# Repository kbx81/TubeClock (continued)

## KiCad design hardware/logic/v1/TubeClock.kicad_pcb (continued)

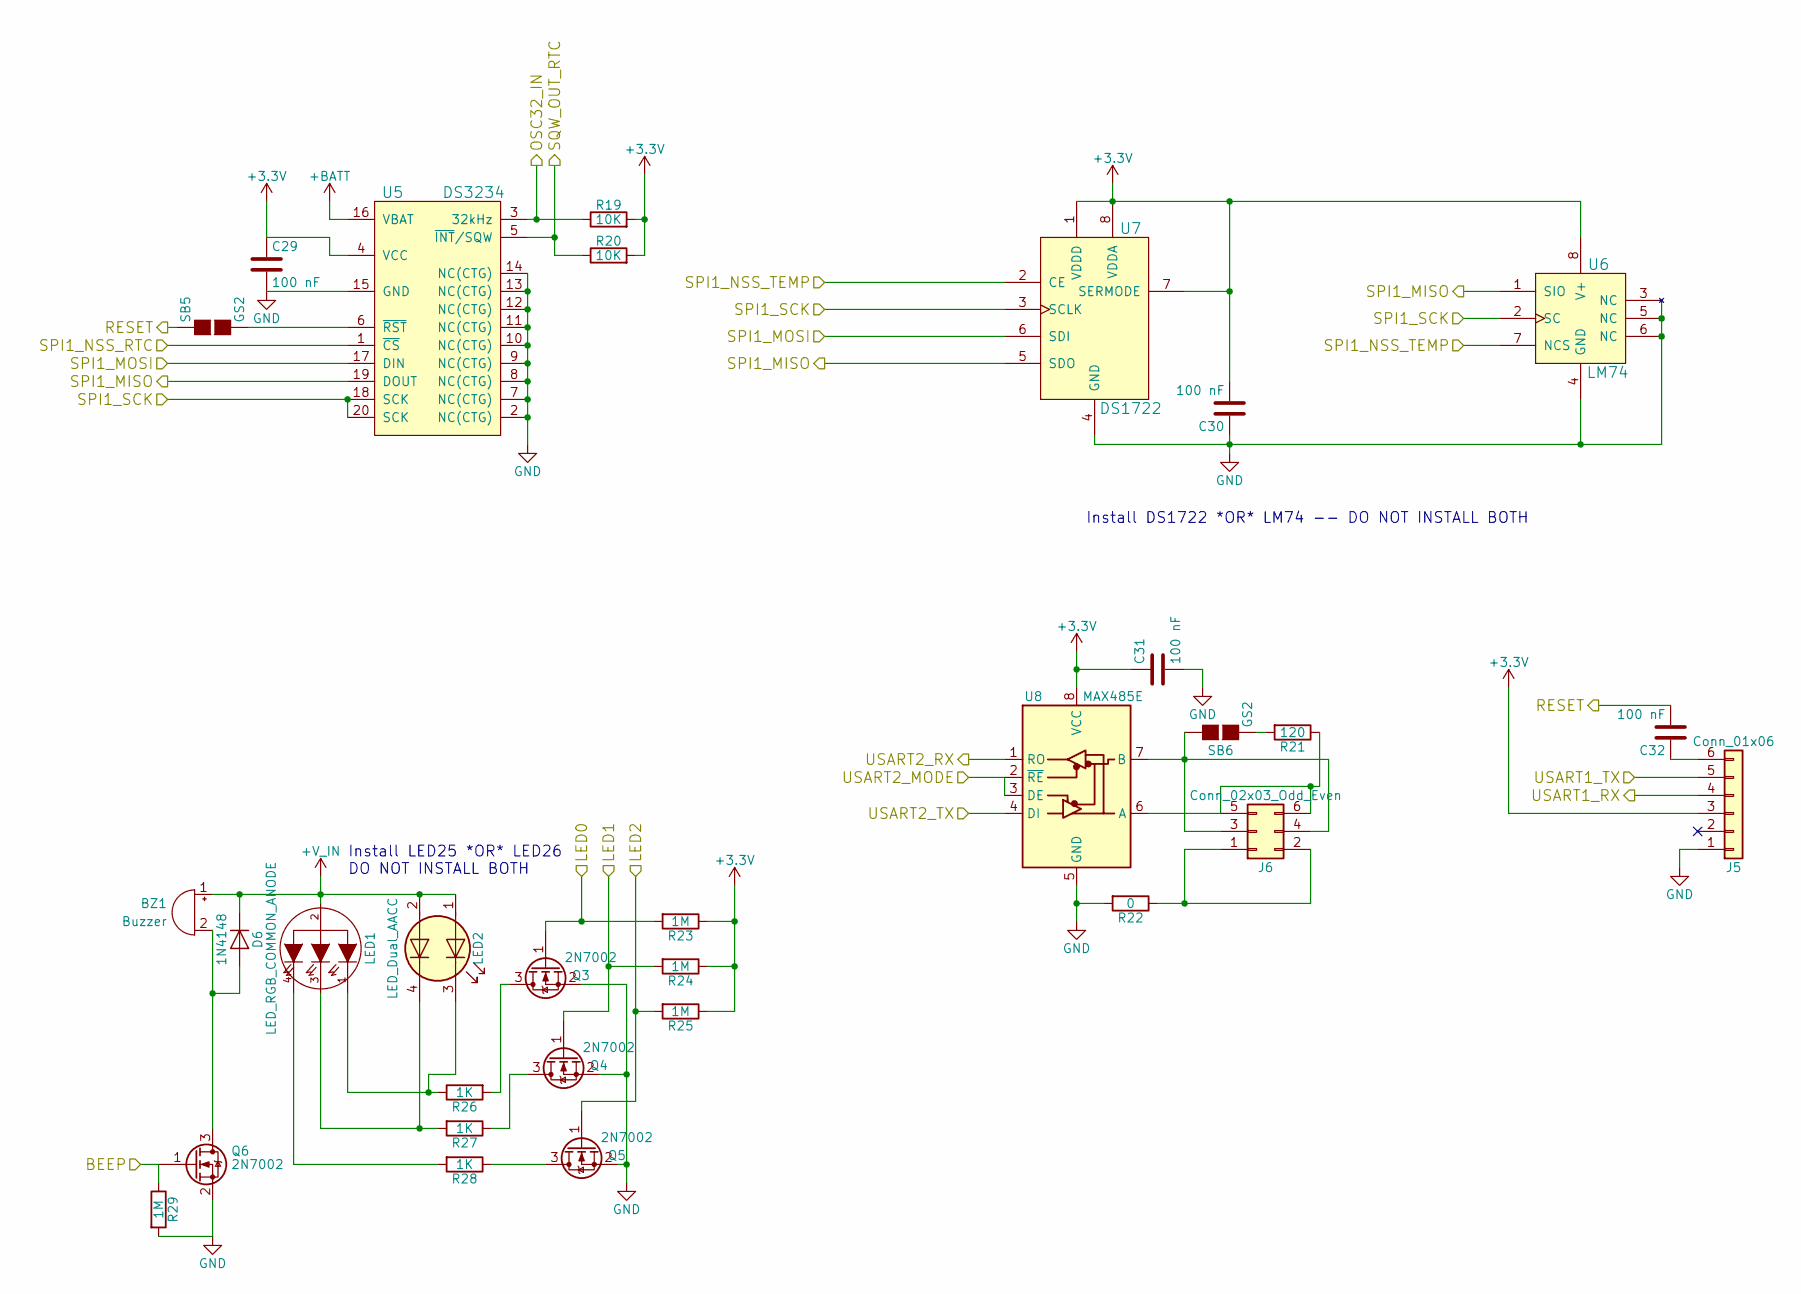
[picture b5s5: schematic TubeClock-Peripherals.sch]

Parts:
BZ1: Buzzer; Buzzer_16x14RM7.6; Part Number TDK SD1614TT-B1
C29, C30, C31, C32: 100 nF; C_0805_2012Metric
D6: 1N4148; D_SOD-123
J5: Conn_01x06; PinHeader_1x06_P2.54mm_Vertical
J6: Conn_02x03_Odd_Even; PinHeader_2x03_P2.54mm_Vertical
LED1: LED_RGB_COMMON_ANODE; LED_D5.0mm-4_RGB
LED2: LED_Dual_AACC; LED_Cree-PLCC4_3.2x2.8mm_CCW; Part Number CMD1522SRUGCTR8
Q3, Q4, Q5, Q6: 2N7002; SOT-23
R19, R20: 10K; R_0805_2012Metric
R21: 120; R_0805_2012Metric
R22: 0; R_0805_2012Metric
R23, R24, R25, R29: 1M; R_0805_2012Metric
R26, R27, R28: 1K; R_0805_2012Metric
SB5, SB6: GS2; SolderJumper-2_P1.3mm_Open_Pad1.0x1.5mm
U5: DS3234; SO-20_12.8x7.5mm_P1.27mm
U6: LM74; SOIC-8_3.9x4.9mm_P1.27mm; Part Number LM74CIMX-3/NOPB
U7: DS1722; SOIC-8_3.9x4.9mm_P1.27mm
U8: MAX485E; SOIC-8_3.9x4.9mm_P1.27mm; Part Number ST1480ACDR

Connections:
+3V3: C29.1, C30.2, C31.1, J5.3, R19.2, R20.2, R23.1, R24.1, R25.1, U5.4 (VCC), U6.8 (V+), U7.1 (VDDD), U7.7 (SERMODE), U7.8 (VDDA), U8.8 (VCC); also elsewhere on the board
+BATT: U5.16 (VBAT); also elsewhere on the board
+V_IN: BZ1.1 (-), D6.1 (K), LED1.2 (COMMON), LED2.1 (A1), LED2.2 (A2); also elsewhere on the board
/TubeClock-Display/SPI1_MOSI: U5.17 (DIN), U7.6 (SDI); also elsewhere on the board
/TubeClock-Display/SPI1_SCK: U5.18 (SCK), U5.20 (SCK), U6.2 (SC), U7.3 (SCLK); also elsewhere on the board
/TubeClock-GPS/RESET: C32.2, SB5.1 (G1); also elsewhere on the board
/TubeClock-GPS/USART1_RX: J5.4; also elsewhere on the board
/TubeClock-GPS/USART1_TX: J5.5; also elsewhere on the board
/TubeClock-MCU/BEEP: Q6.1 (G), R29.1; also elsewhere on the board
/TubeClock-MCU/LED0: Q3.1 (G), R23.2; also elsewhere on the board
/TubeClock-MCU/LED1: Q4.1 (G), R24.2; also elsewhere on the board
/TubeClock-MCU/LED2: Q5.1 (G), R25.2; also elsewhere on the board
/TubeClock-MCU/OSC32_IN: R19.1, U5.3 (32kHz); also elsewhere on the board
/TubeClock-MCU/SPI1_MISO: U5.19 (DOUT), U6.1 (SIO), U7.5 (SDO); also elsewhere on the board
/TubeClock-MCU/SPI1_NSS_RTC: U5.1 (~CS~); also elsewhere on the board
/TubeClock-MCU/SPI1_NSS_TEMP: U6.7 (NCS), U7.2 (CE); also elsewhere on the board
/TubeClock-MCU/USART2_MODE: U8.2 (~RE), U8.3 (DE); also elsewhere on the board
/TubeClock-MCU/USART2_RX: U8.1 (RO); also elsewhere on the board
/TubeClock-MCU/USART2_TX: U8.4 (DI); also elsewhere on the board
/TubeClock-Peripherals/SQW_OUT_RTC: R20.1, U5.5 (~INT~/SQW); also elsewhere on the board
GND: C29.2, C30.1, C31.2, J5.1, Q3.2 (S), Q4.2 (S), Q5.2 (S), Q6.2 (S), R22.2, R29.2, U5.2 (NC(CTG)), U5.7 (NC(CTG)), U5.8 (NC(CTG)), U5.9 (NC(CTG)), U5.10 (NC(CTG)), U5.11 (NC(CTG)), U5.12 (NC(CTG)), U5.13 (NC(CTG)), U5.14 (NC(CTG)), U5.15 (GND), U6.3 (NC), U6.4 (GND), U6.5 (NC), U6.6 (NC), U7.4 (GND), U8.5 (GND); also elsewhere on the board
unnamed: BZ1.2 (+), D6.2 (A), Q6.3 (D)
unnamed: C32.1, J5.6
unnamed: J6.1, J6.2, R22.1
unnamed: J6.3, J6.4, SB6.1 (G1), U8.7 (B)
unnamed: J6.5, J6.6, R21.1, U8.6 (A)
unnamed: LED1.1 (RED), LED2.3 (K1), R26.1
unnamed: LED1.3 (GREEN), LED2.4 (K2), R27.2
unnamed: LED1.4 (BLUE), R28.2
unnamed: Q3.3 (D), R26.2
unnamed: Q4.3 (D), R27.1
unnamed: Q5.3 (D), R28.1
unnamed: R21.2, SB6.2 (G2)
unnamed: SB5.2 (G2), U5.6 (~RST~)

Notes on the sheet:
Install DS1722 *OR* LM74 -- DO NOT INSTALL BOTH
Install LED25 *OR* LED26 DO NOT INSTALL BOTH

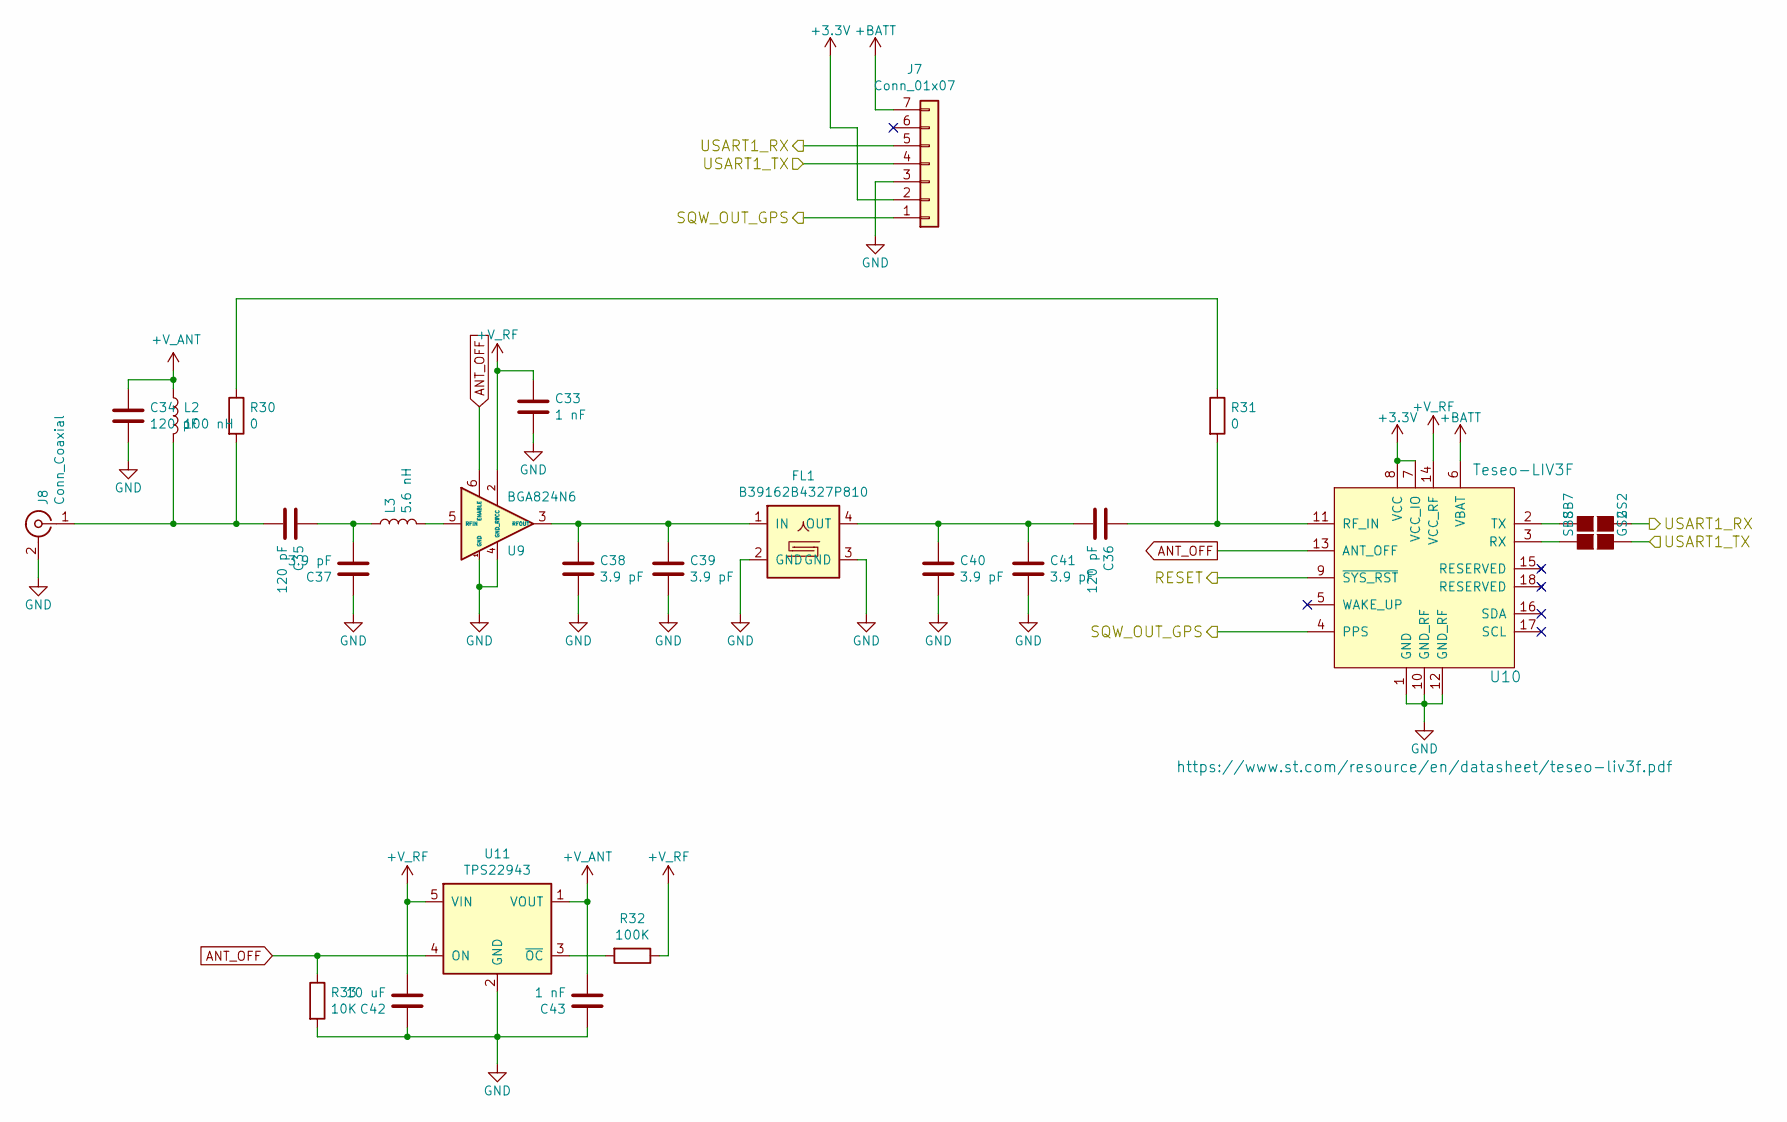
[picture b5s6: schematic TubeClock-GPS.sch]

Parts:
C33, C43: 1 nF; C_0805_2012Metric
C34, C35, C36: 120 pF; C_0402_1005Metric
C37, C38, C39, C40, C41: 3.9 pF; C_0402_1005Metric
C42: 10 uF; C_0805_2012Metric
FL1: B39162B4327P810; Filter_1411-5_1.4x1.1mm
J7: Conn_01x07; PinSocket_1x07_P2.54mm_Vertical
J8: Conn_Coaxial; U.FL_Molex_MCRF_73412-0110_Vertical
L2: 100 nH; L_0402_1005Metric
L3: 5.6 nH; L_0402_1005Metric
R30, R31: 0; R_0402_1005Metric
R32: 100K; R_0805_2012Metric
R33: 10K; R_0805_2012Metric
SB7, SB8: GS2; SolderJumper-2_P1.3mm_Open_Pad1.0x1.5mm
U9: BGA824N6; TSNP-6-2_1.2x0.8mm
U10: Teseo-LIV3F; LCC-18
U11: TPS22943; SOT-353_SC-70-5

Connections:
+3V3: J7.2, U10.7 (VCC_IO), U10.8 (VCC); also elsewhere on the board
+BATT: J7.7, U10.6 (VBAT); also elsewhere on the board
+V_ANT: C34.1, C43.2, L2.1, U11.1 (VOUT)
+V_RF: C33.1, C42.2, R32.1, U9.2 (VCC), U10.14 (VCC_RF), U11.5 (VIN)
/TubeClock-GPS/RESET: U10.9 (~SYS_RST~); also elsewhere on the board
/TubeClock-GPS/SQW_OUT_GPS: J7.1, U10.4 (PPS); also elsewhere on the board
/TubeClock-GPS/USART1_RX: J7.5, SB7.2 (G2); also elsewhere on the board
/TubeClock-GPS/USART1_TX: J7.4, SB8.2 (G2); also elsewhere on the board
ANT_OFF: R33.1, U9.6 (ENABLE), U10.13 (ANT_OFF), U11.4 (ON)
GND: C33.2, C34.2, C37.1, C38.2, C39.2, C40.2, C41.2, C42.1, C43.1, FL1.2 (GND), FL1.3 (GND), FL1.5 (GND), J7.3, J8.2 (Ext), R33.2, U9.1 (GND), U9.4 (GND_RF), U10.1 (GND), U10.10 (GND_RF), U10.12 (GND_RF), U11.2 (GND); also elsewhere on the board
unnamed: C35.1, C37.2, L3.1
unnamed: C35.2, J8.1 (In), L2.2, R30.2
unnamed: C36.1, R31.2, U10.11 (RF_IN)
unnamed: C36.2, C40.1, C41.1, FL1.4 (OUT)
unnamed: C38.1, C39.1, FL1.1 (IN), U9.3 (RFOUT)
unnamed: L3.2, U9.5 (RFIN)
unnamed: R30.1, R31.1
unnamed: R32.2, U11.3 (~OC~)
unnamed: SB7.1 (G1), U10.2 (TX)
unnamed: SB8.1 (G1), U10.3 (RX)

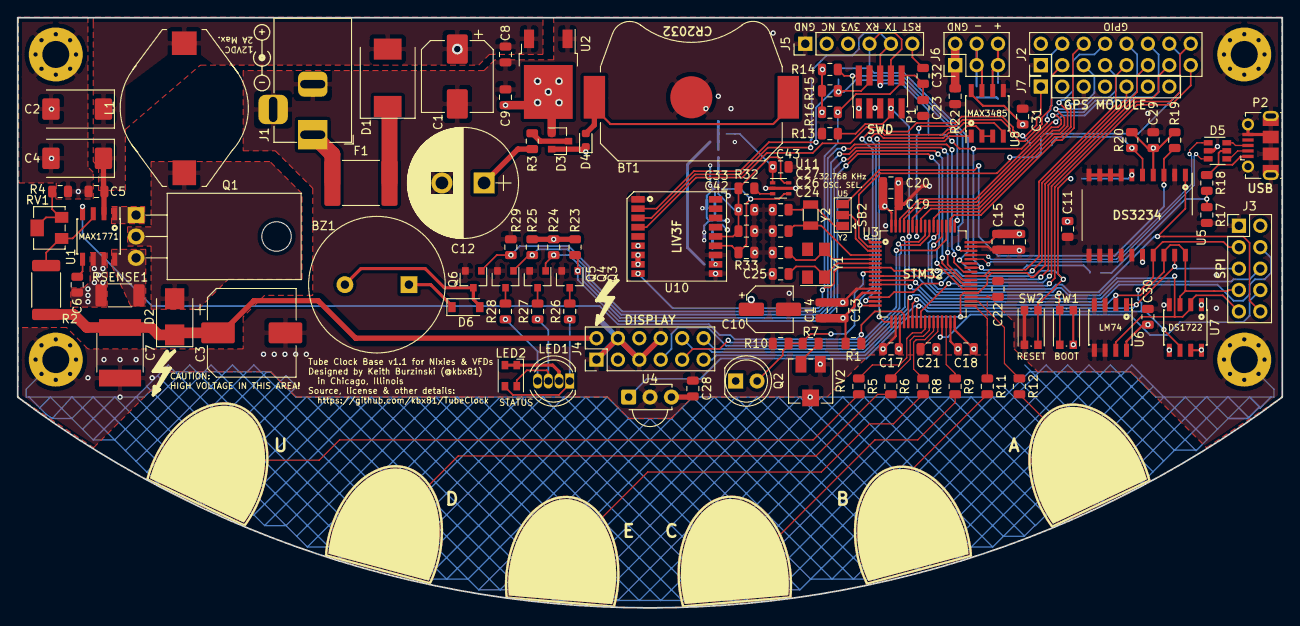
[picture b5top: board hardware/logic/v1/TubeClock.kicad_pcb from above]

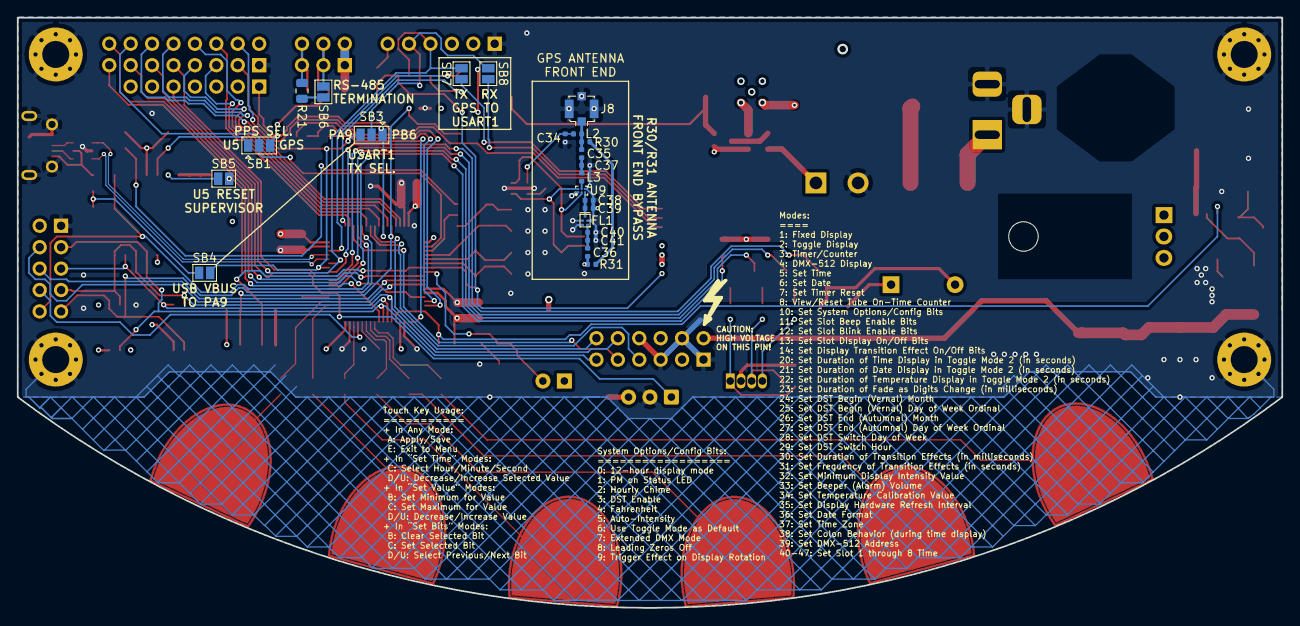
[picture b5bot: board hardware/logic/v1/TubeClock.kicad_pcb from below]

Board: 4 copper layers, 150.0 x 70.0 mm, 143 parts (23 on the bottom side), 111 nets.

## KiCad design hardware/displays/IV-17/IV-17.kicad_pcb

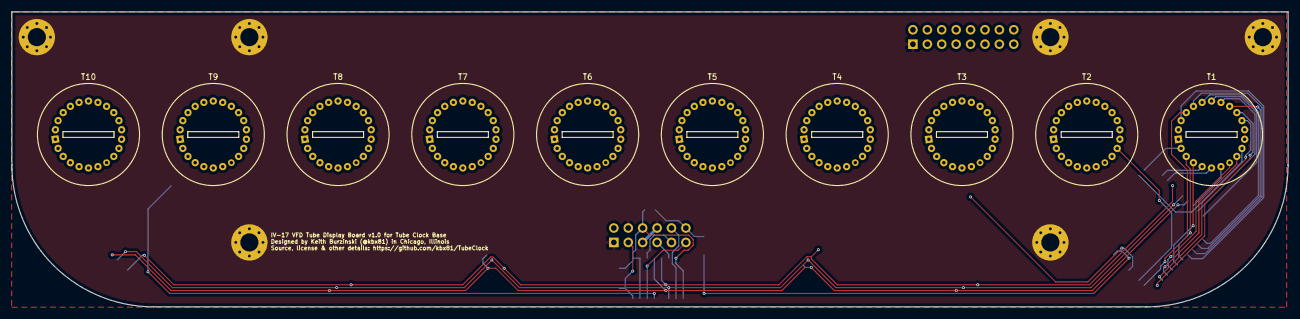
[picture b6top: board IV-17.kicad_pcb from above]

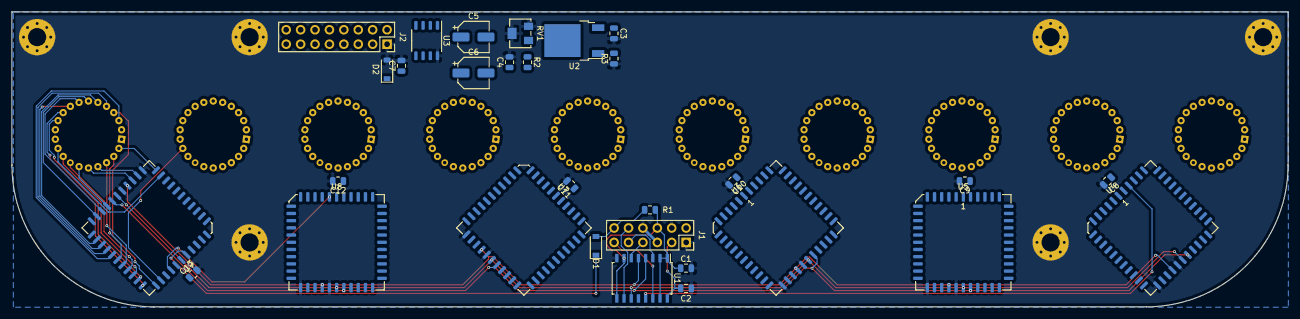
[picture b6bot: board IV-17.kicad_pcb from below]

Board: 2 copper layers, 225.0 x 52.0 mm, 46 parts (30 on the bottom side), 212 nets.

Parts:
C1, C2, C8, C9, C10, C11, C12, C13: 100 nF; C_0805_2012Metric
C3, C4: 10 uF; C_0805_2012Metric
C5, C6: 47 uF; CP_Elec_5x5.8
C7: 1 uF; C_0805_2012Metric
D1: 1N4148; D_SOD-123
D2: D_Zener 2.4 V; D_SOD-123
H1, H2, H3, H4, H5, H6: MountingHole_Pad; MountingHole_3.2mm_M3_Pad_Via
J1: Conn_02x06_Odd_Even; PinSocket_2x06_P2.54mm_Vertical
J2: Conn_02x08_Odd_Even; PinSocket_2x08_P2.54mm_Vertical
R1: 10K; R_0805_2012Metric
R2: 120; R_0805_2012Metric
R3: 420; R_0805_2012Metric
RV1: 1K; Potentiometer_Bourns_3214W_Vertical
T1, T2, T3, T4, T5, T6, T7, T8, T9, T10: IV-17
U1: CD40109B; SOIC-16W_5.3x10.2mm_P1.27mm
U2: LD1117ADT-TR_TO-252-2; TO-252-2
U3: BD6211F; SSOP-8_3.9x5.05mm_P1.27mm
U4, U5, U6, U7, U8, U9: MAX6934; PLCC-44_16.6x16.6mm_P1.27mm

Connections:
+3V3: C1.1, J1.6, R1.1, U1.1, U1.2, U1.7, U1.9, U1.15
+V_HV: J1.2, T1.12, T2.12, T3.12, T4.12, T5.12, T6.12, T7.12, T8.12, T9.12, T10.12, U4.1, U5.1, U6.1, U7.1, U8.1, U9.1
+V_IN: C2.1, C3.1, C8.1, C9.1, C10.1, C11.1, C12.1, C13.1, J1.3, U1.16, U2.3, U4.44, U5.44, U6.44, U7.44, U8.44, U9.44
BLANK: U1.5, U4.21, U5.21, U6.21, U7.21, U8.21, U9.21
BLANK_DB: J1.7, U1.6
CLK: U1.11, U4.23, U5.23, U6.23, U7.23, U8.23, U9.23
CLK_DB: J1.10, U1.10
DATA_IN: U1.13, U4.43
DATA_IN_DB: J1.11, U1.14
DATA_OUT: D1.1, U9.2
DATA_THROUGH1: U4.2, U5.43
DATA_THROUGH2: U5.2, U6.43
DATA_THROUGH3: U6.2, U7.43
DATA_THROUGH4: U7.2, U8.43
DATA_THROUGH5: U8.2, U9.43
FILAMENT_AC1: C6.2, T1.11, T4.1, T5.11, T8.1, T9.11
FILAMENT_AC2: C5.2, T2.1, T3.11, T6.1, T7.11, T10.1
FILAMENT_CT: C7.1, D2.1, T3.1, T4.11
GND: C1.2, C2.2, C3.2, C4.2, C7.2, C8.2, C9.2, C10.2, C11.2, C12.2, C13.2, D2.2, H1.1, H2.1, H3.1, H4.1, H5.1, H6.1, J1.1, J1.4, J1.5, J1.8, J2.1, R3.1, RV1.2, RV1.3, U1.8, U3.8, U4.18, U4.22, U5.18, U5.22, U6.18, U6.22, U7.18, U7.22, U8.18, U8.22, U9.18, U9.22
LOAD: U1.4, U4.24, U5.24, U6.24, U7.24, U8.24, U9.24
LOAD_DB: J1.9, U1.3
unnamed: C4.1, R2.2, U2.2, U3.2, U3.3, U3.6
unnamed: C5.1, U3.1
unnamed: C6.1, U3.7
unnamed: D1.2, J1.12, R1.2
unnamed: R2.1, R3.2, RV1.1, U2.1
unnamed: T1.1, T2.11
unnamed: T5.1, T6.11
unnamed: T7.1, T8.11
unnamed: T9.1, T10.11
T1_A_A1: T1.20, U9.40
T1_A_A2: T1.14, U9.39
T1_A_B: T1.13, U9.38
T1_A_C: T1.9, U9.37
T1_A_D1: T1.4, U9.35
T1_A_D2: T1.8, U9.36
T1_A_E: T1.3, U9.34
T1_A_F: T1.21, U9.33
T1_A_G1: T1.19, U9.32
T1_A_G2: T1.15, U9.31
T1_A_H: T1.18, U9.30
T1_A_J: T1.17, U9.27
T1_A_K: T1.16, U9.26
T1_A_L: T1.7, U9.25
T1_A_M: T1.6, U9.20
T1_A_N: T1.5, U9.19
T1_A_PL: T1.2, U9.17
T1_A_PR: T1.10, U9.16
T2_A_A1: T2.20, U8.20
T2_A_A2: T2.14, U8.19
T2_A_B: T2.13, U8.17
T2_A_C: T2.9, U8.16
T2_A_D1: T2.4, U8.14
T2_A_D2: T2.8, U8.15
T2_A_E: T2.3, U8.13
T2_A_F: T2.21, U8.12
T2_A_G1: T2.19, U8.11
T2_A_G2: T2.15, U8.10
T2_A_H: T2.18, U8.9
T2_A_J: T2.17, U8.8
T2_A_K: T2.16, U8.7
T2_A_L: T2.7, U8.5
T2_A_M: T2.6, U8.4
T2_A_N: T2.5, U8.3
T2_A_PL: T2.2, U9.42
T2_A_PR: T2.10, U9.41
T3_A_A1: T3.20, U7.4
T3_A_A2: T3.14, U7.3
T3_A_B: T3.13, U8.42
T3_A_C: T3.9, U8.41
T3_A_D1: T3.4, U8.39
T3_A_D2: T3.8, U8.40
T3_A_E: T3.3, U8.38
T3_A_F: T3.21, U8.37
T3_A_G1: T3.19, U8.36
T3_A_G2: T3.15, U8.35
T3_A_H: T3.18, U8.34
T3_A_J: T3.17, U8.33
T3_A_K: T3.16, U8.32
T3_A_L: T3.7, U8.31
T3_A_M: T3.6, U8.30
T3_A_N: T3.5, U8.27
T3_A_PL: T3.2, U8.26
T3_A_PR: T3.10, U8.25
T4_A_A1: T4.20, U7.30
T4_A_A2: T4.14, U7.27
T4_A_B: T4.13, U7.26
T4_A_C: T4.9, U7.25
T4_A_D1: T4.4, U7.19
T4_A_D2: T4.8, U7.20
T4_A_E: T4.3, U7.17
T4_A_F: T4.21, U7.16
T4_A_G1: T4.19, U7.15
T4_A_G2: T4.15, U7.14
T4_A_H: T4.18, U7.13
T4_A_J: T4.17, U7.12
T4_A_K: T4.16, U7.11
T4_A_L: T4.7, U7.10
T4_A_M: T4.6, U7.9
T4_A_N: T4.5, U7.8
T4_A_PL: T4.2, U7.7
T4_A_PR: T4.10, U7.5
T5_A_A1: T5.20, U6.9
T5_A_A2: T5.14, U6.8
T5_A_B: T5.13, U6.7
T5_A_C: T5.9, U6.5
T5_A_D1: T5.4, U6.3
T5_A_D2: T5.8, U6.4
T5_A_E: T5.3, U7.42
T5_A_F: T5.21, U7.41
T5_A_G1: T5.19, U7.40
T5_A_G2: T5.15, U7.39
T5_A_H: T5.18, U7.38
T5_A_J: T5.17, U7.37
T5_A_K: T5.16, U7.36
T5_A_L: T5.7, U7.35
T5_A_M: T5.6, U7.34
T5_A_N: T5.5, U7.33
T5_A_PL: T5.2, U7.32
T5_A_PR: T5.10, U7.31
T6_A_A1: T6.20, U6.34
T6_A_A2: T6.14, U6.33
T6_A_B: T6.13, U6.32
T6_A_C: T6.9, U6.31
T6_A_D1: T6.4, U6.27
T6_A_D2: T6.8, U6.30
T6_A_E: T6.3, U6.26
T6_A_F: T6.21, U6.25
T6_A_G1: T6.19, U6.20
T6_A_G2: T6.15, U6.19
T6_A_H: T6.18, U6.17
T6_A_J: T6.17, U6.16
T6_A_K: T6.16, U6.15
T6_A_L: T6.7, U6.14
T6_A_M: T6.6, U6.13
T6_A_N: T6.5, U6.12
T6_A_PL: T6.2, U6.11
T6_A_PR: T6.10, U6.10
T7_A_A1: T7.20, U5.13
T7_A_A2: T7.14, U5.12
T7_A_B: T7.13, U5.11
T7_A_C: T7.9, U5.10
T7_A_D1: T7.4, U5.8
T7_A_D2: T7.8, U5.9
T7_A_E: T7.3, U5.7
T7_A_F: T7.21, U5.5
T7_A_G1: T7.19, U5.4
T7_A_G2: T7.15, U5.3
T7_A_H: T7.18, U6.42
T7_A_J: T7.17, U6.41
T7_A_K: T7.16, U6.40
T7_A_L: T7.7, U6.39
T7_A_M: T7.6, U6.38
T7_A_N: T7.5, U6.37
T7_A_PL: T7.2, U6.36
T7_A_PR: T7.10, U6.35
T8_A_A1: T8.20, U5.38
T8_A_A2: T8.14, U5.37
T8_A_B: T8.13, U5.36
T8_A_C: T8.9, U5.35
T8_A_D1: T8.4, U5.33
T8_A_D2: T8.8, U5.34
T8_A_E: T8.3, U5.32
T8_A_F: T8.21, U5.31
T8_A_G1: T8.19, U5.30
T8_A_G2: T8.15, U5.27
T8_A_H: T8.18, U5.26
T8_A_J: T8.17, U5.25
T8_A_K: T8.16, U5.20
T8_A_L: T8.7, U5.19
T8_A_M: T8.6, U5.17
T8_A_N: T8.5, U5.16
T8_A_PL: T8.2, U5.15
T8_A_PR: T8.10, U5.14
T9_A_A1: T9.20, U4.17
T9_A_A2: T9.14, U4.16
T9_A_B: T9.13, U4.15
T9_A_C: T9.9, U4.14
T9_A_D1: T9.4, U4.12
T9_A_D2: T9.8, U4.13
T9_A_E: T9.3, U4.11
T9_A_F: T9.21, U4.10
T9_A_G1: T9.19, U4.9
T9_A_G2: T9.15, U4.8
T9_A_H: T9.18, U4.7
T9_A_J: T9.17, U4.5
T9_A_K: T9.16, U4.4
T9_A_L: T9.7, U4.3
T9_A_M: T9.6, U5.42
T9_A_N: T9.5, U5.41
T9_A_PL: T9.2, U5.40
T9_A_PR: T9.10, U5.39
T10_A_A1: T10.20, U4.42
T10_A_A2: T10.14, U4.41
T10_A_B: T10.13, U4.40
T10_A_C: T10.9, U4.39
T10_A_D1: T10.4, U4.37
T10_A_D2: T10.8, U4.38
T10_A_E: T10.3, U4.36
T10_A_F: T10.21, U4.35
T10_A_G1: T10.19, U4.34
T10_A_G2: T10.15, U4.33
T10_A_H: T10.18, U4.32
T10_A_J: T10.17, U4.31
T10_A_K: T10.16, U4.30
T10_A_L: T10.7, U4.27
T10_A_M: T10.6, U4.26
T10_A_N: T10.5, U4.25
T10_A_PL: T10.2, U4.20
T10_A_PR: T10.10, U4.19
TIM_CH1: J2.7, U3.4
TIM_CH1N: J2.12, U3.5

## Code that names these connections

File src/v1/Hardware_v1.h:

//
// kbx81's tube clock Hardware class pin definitions
// ---------------------------------------------------------------------------
// (c)2019 by kbx81. See LICENSE for details.
//
// This program is free software: you can redistribute it and/or modify
// it under the terms of the GNU Lesser General Public License as published by
// the Free Software Foundation, either version 3 of the License, or
// (at your option) any later version.
//
// This program is distributed in the hope that it will be useful,
// but WITHOUT ANY WARRANTY; without even the implied warranty of
// MERCHANTABILITY or FITNESS FOR A PARTICULAR PURPOSE.  See the
// GNU Lesser General Public License for more details.
//
// You should have received a copy of the GNU Lesser General Public License
// along with this program.  If not, see <http://www.gnu.org/licenses/>
//
#pragma once

#include <cstdint>
#include <libopencm3/cm3/nvic.h>
#include <libopencm3/stm32/dma.h>
#include <libopencm3/stm32/gpio.h>
#include <libopencm3/stm32/syscfg.h>
#include <libopencm3/stm32/timer.h>
#include <libopencm3/stm32/tsc.h>
#include <libopencm3/stm32/usart.h>

namespace kbxTubeClock::Hardware {

#ifdef ENABLE_PROFILING
// ISR profiling I/O port & pin (active when ENABLE_PROFILING is defined)
//
static const auto cProfilingPort = GPIOA;
static const auto cProfilingPin = GPIO15;
#endif

// USART assignments
//
static const auto cGpsUsart = USART1;
static const auto cDmxUsart = USART2;
static const auto cSerialRemoteUsartRx = USART3;
static const auto cSerialRemoteUsartTx = USART4;

// USART Tx and Rx ports, pins, & IRQs
//
// static const auto cUsart1Port = GPIOA;
static const auto cUsart1RxPort = GPIOA;
static const auto cUsart1RxPin = GPIO10;
static const auto cUsart1RxAF = GPIO_AF1;
static const auto cUsart1TxPort = GPIOB;
static const auto cUsart1TxPin = GPIO6;
static const auto cUsart1TxAF = GPIO_AF0;
static const auto cUsart1Irq = NVIC_USART1_IRQ;

static const auto cUsart2Port = GPIOA;
// static const auto cUsart2RxPort = GPIOA;
static const auto cUsart2RxPin = GPIO3;
// static const auto cUsart2RxAF   = GPIO_AF1;
// static const auto cUsart2TxPort = GPIOA;
static const auto cUsart2TxPin = GPIO2;
// static const auto cUsart2TxAF   = GPIO_AF1;
// static const auto cUsart2DePort = GPIOA;
static const auto cUsart2DePin = GPIO1;
// static const auto cUsart2DeAF   = GPIO_AF1;
static const auto cUsart2AF = GPIO_AF1;
static const auto cUsart2Irq = NVIC_USART2_IRQ;

// USART3: Serial remote control RX (PB10 with TX/RX swap)
static const auto cUsart3RxPort = GPIOB;
static const auto cUsart3RxPin = GPIO10;
static const auto cUsart3RxAF = GPIO_AF4;
// USART4: Serial remote control TX (PA0)
static const auto cUsart4TxPort = GPIOA;
static const auto cUsart4TxPin = GPIO0;
static const auto cUsart4TxAF = GPIO_AF4;
// USART3 and USART4 share a single IRQ on STM32F072
static const auto cUsart3_4Irq = NVIC_USART3_4_IRQ;

// external alarm input port(s) & pins
//
static const auto cAlarmInputPort = GPIOC;
static const uint8_t cAlarmInputPinCount = 4;
static const uint16_t cAlarmInputPins[cAlarmInputPinCount] = {GPIO1, GPIO4, GPIO9, GPIO13};

// buzzer I/O port & pin
//
static const auto cBuzzerPort = GPIOA;
static const auto cBuzzerPin = GPIO8;
static const auto cBuzzerTimer = TIM1;
static const auto cBuzzerTimerOC = TIM_OC1;

// status LED I/O port(s) & pins
//
static const auto cLedPort = GPIOC;
static const auto cLed0Pin = GPIO6;
static const auto cLed1Pin = GPIO7;
static const auto cLed2Pin = GPIO8;

static const auto cLedPortAF = GPIO_AF0;

static const auto cLedPwmTimer = TIM3;
static const auto cLed0PwmOc = TIM_OC1;
static const auto cLed1PwmOc = TIM_OC2;
static const auto cLed2PwmOc = TIM_OC3;

// timer used for tube display PWM generation and associated IRQ
//
static const auto cTubePwmTimer = TIM2;
static const auto cTubePwmTimerIrq = NVIC_TIM2_IRQ;

// phototransistor I/O port, pin, and ADC channel
//
static const auto cPhototransistorPort = GPIOC;
static const auto cPhototransistorPin = GPIO0;
static const uint8_t cPhototransistorChannel = 10;

// IR demodulator I/O port, pin, and timer
//
static const auto cIrPort = GPIOB;
static const auto cIrPin = GPIO15;
static const auto cIrTimer = TIM7;
static const auto cIrTimerIrq = NVIC_TIM7_IRQ;

// Pulse-Per-Second (SQW) I/O port, pin, & IRQ
//
static const auto cPpsPort = GPIOC;
static const auto cPpsPin = GPIO13;
static const auto cPpsIrq = NVIC_EXTI4_15_IRQ;

// I2C ports & pins
//
static const auto cI2c1Port = GPIOB;
static const auto cI2c1SlcPin = GPIO8;
static const auto cI2c1SdaPin = GPIO9;

// SPI ports & pins
//
static const auto cSpi1Port = GPIOA;
static const auto cSpi1AltPort = GPIOB;
static const auto cSpi1SckPin = GPIO5;
static const auto cSpi1MisoPin = GPIO6;
static const auto cSpi1MosiPin = GPIO7;
static const auto cSpi1MisoDisplayPin = GPIO4;

// SPI NSS I/O port & pins
//
static const auto cNssPort = GPIOC;
static const auto cNssDisplayPin = GPIO10;
static const auto cNssRtcPin = GPIO11;
static const auto cNssTemperaturePin = GPIO12;

// driver blank I/O port & pin
static const auto cBlankDisplayPort = GPIOB;
static const auto cBlankDisplayPin = GPIO3;

// high voltage shutdown I/O port & pin
//
static const auto cHvShutdownPort = GPIOA;
static const auto cHvShutdownPin = GPIO4;

// DMA channel assignments and remapping via SYSCFG_CFGR1
//
static const auto cAdcDmaChannel = DMA_CHANNEL1;
static const auto cSpi1RxDmaChannel = DMA_CHANNEL2;
static const auto cSpi1TxDmaChannel = DMA_CHANNEL3;
static const auto cI2c1RxDmaChannel = 0;
static const auto cI2c1TxDmaChannel = 0;
static const auto cUsart1RxDmaChannel = DMA_CHANNEL5;
static const auto cUsart1TxDmaChannel = DMA_CHANNEL4;
static const auto cUsart2RxDmaChannel = DMA_CHANNEL6;
static const auto cUsart2TxDmaChannel = DMA_CHANNEL7;
// USART1 and USART2 TX and RX remap bits set in SYSCFG_CFGR1 since
//  SPI1 ties up the USART's default DMA channels
static const auto cDmaChannelRemaps =
    SYSCFG_CFGR1_USART1_RX_DMA_RMP | SYSCFG_CFGR1_USART1_TX_DMA_RMP | SYSCFG_CFGR1_USART2_DMA_RMP;

// DMA interrupts we use
//
static const auto cDmaIrqSpi1 = NVIC_DMA1_CHANNEL2_3_DMA2_CHANNEL1_2_IRQ;
static const auto cDmaIrqUsarts = NVIC_DMA1_CHANNEL4_7_DMA2_CHANNEL3_5_IRQ;

// number of TSC channels we're using
//
static const uint8_t cTscChannelCount = 6;

// number of TSC channels we're using per group
//
static const uint8_t cTscChannelsPerGroup = 3;

// TSC IRQ
//
static const uint8_t cTscIrq = NVIC_TSC_IRQ;

// touch sense controller I/O groups
//
static const auto cTscGroupControlBits = TSC_IOGCSR_GxE(3) | TSC_IOGCSR_GxE(6);

// touch sensing controller I/O port
//
static const auto cTscPort = GPIOB;
static const auto cTscPortC = GPIOC;

// pins used for sense capacitors
//
static const auto cTscSamplingCapPins = GPIO2 | GPIO14;

// pins used for touch keys
//
static const auto cTscTouchKeyPins = GPIO0 | GPIO1 | GPIO11 | GPIO12 | GPIO13;
static const auto cTscTouchKeyPinsC = GPIO5;

// touch sense controller I/O groups
//
static const uint32_t cTscChannelControlBits[] = {
    (1 << 8) | (1 << 20),
    (1 << 9) | (1 << 21),
    (1 << 10) | (1 << 22),
};

// touch sense controller I/O groups
//
static const uint32_t cTscSamplingControlBits = (1 << 11) | (1 << 23);

}  // namespace kbxTubeClock::Hardware

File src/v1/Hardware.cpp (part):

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        cUsart3AutoBaud,      // Auto-baud (disabled)
        cUsart3DataBits,      // Number of data bits
        cUsart3DriverEnable,  // DE output (disabled)
        cUsart3SwapTxRx       // TX/RX pin swap (PB10 is normally TX, swapped to RX)
    },
    {
        cUsart4BaudRate,      // Baud rate
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// flag set when any temperature reading is updated; cleared by temperatureUpdated()
static volatile bool _temperatureUpdated = false;

// state of the BLANK pin
//
static bool _displayBlankingState = true;

// indicates to setDisplayBlankPin() that it should NOT clear the BLANK pin as
//  a display write is in progress with flicker reduction active
volatile static bool _displayBlankForWrite = false;

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//
static bool _externalRtcConnected = false;

// state of the HV SHUTDOWN pin
//
static bool _hvState = false;

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
  // Configure the SPI NSS pins for the HV drivers, RTC, and temp sensor
  gpio_mode_setup(cNssPort, GPIO_MODE_OUTPUT, GPIO_PUPD_NONE, cNssDisplayPin | cNssRtcPin | cNssTemperaturePin);
  // Configure the BLANK pin for the LED drivers
  gpio_mode_setup(cBlankDisplayPort, GPIO_MODE_OUTPUT, GPIO_PUPD_NONE, cBlankDisplayPin);
  // Configure the analog input pin for the phototransistor
  gpio_mode_setup(cPhototransistorPort, GPIO_MODE_ANALOG, GPIO_PUPD_NONE, cPhototransistorPin);
  // Configure the SHUTDOWN pin for the boost converter
  gpio_mode_setup(cHvShutdownPort, GPIO_MODE_OUTPUT, GPIO_PUPD_NONE, cHvShutdownPin);

  // Set the inital pin states for the pins we configured above
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    gpio_mode_setup(cAlarmInputPort, GPIO_MODE_INPUT, GPIO_PUPD_PULLUP, cAlarmInputPins[i]);
  }

  // Next, configure the external PPS/SQW_In pulse-per-second input pin and interrupt
  // Trigger only on rising edge to avoid double-triggering on square wave PPS signal
  gpio_mode_setup(cPpsPort, GPIO_MODE_INPUT, GPIO_PUPD_NONE, cPpsPin);
  exti_select_source(EXTI13, cPpsPort);
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}

void _i2cSetup() {
  // Configure GPIOs SCL=PB8 and SDA=PB9 so we can reset the bus nicely
  gpio_mode_setup(cI2c1Port, GPIO_MODE_OUTPUT, GPIO_PUPD_PULLUP, cI2c1SlcPin | cI2c1SdaPin);
  gpio_set_output_options(cI2c1Port, GPIO_OTYPE_OD, GPIO_OSPEED_100MHZ, cI2c1SlcPin | cI2c1SdaPin);

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
  // Setup SPI1 pins as alternate function zero
  gpio_set_af(cSpi1Port, GPIO_AF0, cSpi1SckPin | cSpi1MisoPin | cSpi1MosiPin);
  // MISO=PB4 from HV drivers
  gpio_set_af(cSpi1AltPort, GPIO_AF0, cSpi1MisoDisplayPin);
  // Configure GPIOs
  gpio_mode_setup(cSpi1Port, GPIO_MODE_AF, GPIO_PUPD_NONE, cSpi1SckPin | cSpi1MosiPin);
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
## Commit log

2019-07-30 Initial commit. Yay\!
2019-07-30 Added photos link
2019-07-30 Copy updates
2019-08-02 Updated BoMs with more notes
2019-08-02 BoM copy updates
2019-08-02 Copy fixes and updates
2019-08-05 Added GPS build documentation
2019-08-07 Updated component specs
2019-08-18 Tweaks
2019-09-05 Mostly working...
2019-09-08 It all finally works
2019-09-08 Added binary
2019-09-11 Added Usart interface class
2019-09-11 Relaxed SPI clock a lil' bit
2019-10-07 DMX-512 implementation and other fixes/updates
2020-02-23 Various updates
2020-04-11 BoM tweak
2020-04-11 Added Octopart links
2024-12-19 Add Display board for Burroughs B-5991 Nixie Tubes (aka 8422), also supplied by National
2026-01-19 A few years later...
2026-01-19 Hot path optimization
2026-02-10 optimize, fix, preen
2026-02-11 status
2026-02-15 serial, tune
2026-02-16 fix, preen
2026-02-17 tune
2026-02-18 temp + offset
2026-02-22 led, rtttl, fix, preen
2026-02-23 queue
2026-02-24 animations
2026-02-24 version
2026-02-24 boot
2026-02-25 build
2026-02-26 build, keys, ota, timer
2026-02-28 preen
2026-02-28 alarm
2026-02-28 fix, optimize
2026-03-02 bump
2026-03-06 format, tidy
2026-03-07 refactor settings
2026-03-08 sram
2026-03-09 media
2026-03-10 wifi
2026-03-14 copy
2026-03-15 automation
2026-03-15 Release 26.03.01
2026-03-15 move
2026-03-23 gps, usart, preen
